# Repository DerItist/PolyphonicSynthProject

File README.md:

# PolyphonicSynthProject
All about building my own polyphonic synthesizer.

I use the open source tool KICAD for the schematics and pcb design.

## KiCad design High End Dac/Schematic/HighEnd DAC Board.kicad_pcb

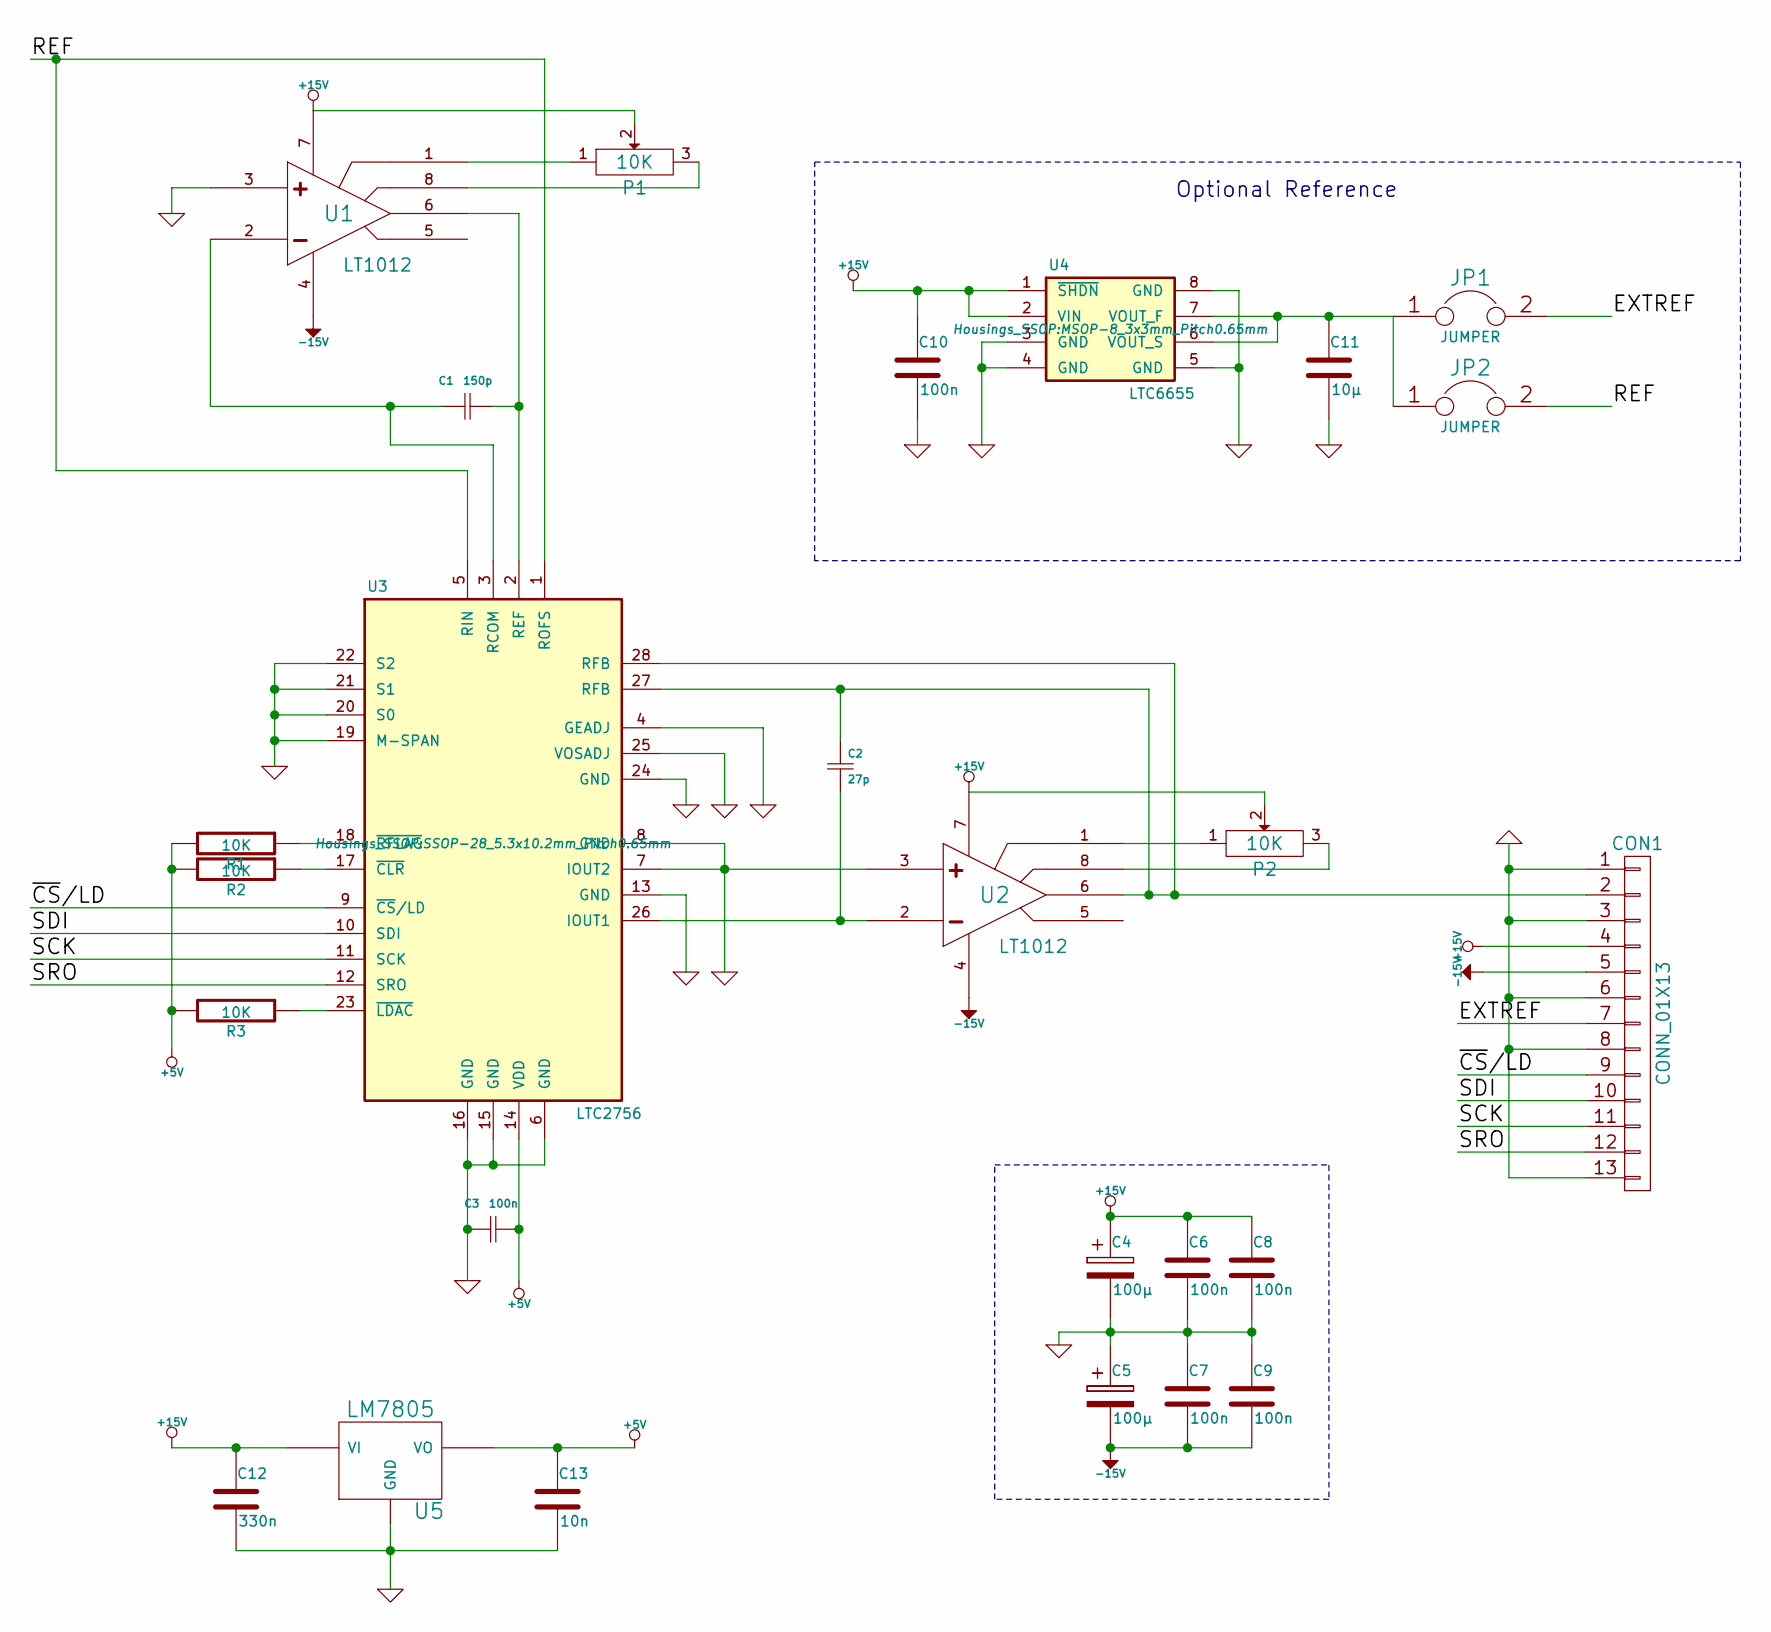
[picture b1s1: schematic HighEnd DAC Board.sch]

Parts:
C1: 150p; C_Disc_D3_P2.5
C2: 27p; C_Disc_D3_P2.5
C3: 100n; C_0805_HandSoldering
C4, C5: 100µ; Elko_vert_20x10mm_RM2.5to5_CopperClear
C6, C7, C8, C9, C10: 100n; C_Disc_D3_P2.5
C11: 10µ; C_Rect_L7.5_W6.5_P5
C12: 330n; C_Rect_L7.5_W6.5_P5
C13: 10n; C_Disc_D3_P2.5
CON1: CONN_01X13; DB15FD
JP1, JP2: JUMPER; Pin_Header_Straight_1x02
P1, P2: 10K; Potentiometer_Bourns_3296X_3-8Zoll_Inline_ScrewFront
R1, R2, R3: 10K; Resistor_Horizontal_RM10mm
U1, U2: LT1012; DIP-8__300_ELL
U3: LTC2756; SSOP-28_5.3x10.2mm_Pitch0.65mm
U4: LTC6655; MSOP-8_3x3mm_Pitch0.65mm
U5: LM7805; LM78XX-TO92

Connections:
+5V: C3.2, C13.1, R1.2, R2.2, R3.2, U3.14 (VDD), U5.VO
+15V: C4.1, C6.1, C8.1, C10.1, C12.1, CON1.4, P1.2, P2.2, U1.7 (V+), U2.7 (V+), U4.1 (~SHDN~), U4.2 (VIN), U5.VI
-15V: C5.2, C7.2, C9.2, CON1.5, U1.4 (V-), U2.4 (V-)
/EXTREF: CON1.7, JP1.2
/REF: JP2.2, U3.1 (ROFS), U3.5 (RIN)
/SCK: CON1.11, U3.11 (SCK)
/SDI: CON1.10, U3.10 (SDI)
/SRO: CON1.12, U3.12 (SRO)
/~CS~/LD: CON1.9, U3.9 (~CS~/LD)
GND: C3.1, C4.2, C5.1, C6.2, C7.1, C8.2, C9.1, C10.2, C11.2, C12.2, C13.2, CON1.1, CON1.3, CON1.6, CON1.8, CON1.13, U1.3 (NON), U2.3 (NON), U3.4 (GEADJ), U3.6 (GND), U3.7 (IOUT2), U3.8 (GND), U3.13 (GND), U3.15 (GND), U3.16 (GND), U3.19 (M-SPAN), U3.20 (S0), U3.21 (S1), U3.22 (S2), U3.24 (GND), U3.25 (VOSADJ), U4.3 (GND), U4.4 (GND), U4.5 (GND), U4.8 (GND), U5.GND
unnamed: C1.1, U1.2 (INVERTING), U3.3 (RCOM)
unnamed: C1.2, U1.6 (OUTPUT), U3.2 (REF)
unnamed: C2.1, CON1.2, U2.6 (OUTPUT), U3.27 (RFB), U3.28 (RFB)
unnamed: C2.2, U2.2 (INVERTING), U3.26 (IOUT1)
unnamed: C11.1, JP1.1, JP2.1, U4.6 (VOUT_S), U4.7 (VOUT_F)
unnamed: P1.1, U1.1 (VOS/TRIM)
unnamed: P1.3, U1.8 (VOS/TRIM)
unnamed: P2.1, U2.1 (VOS/TRIM)
unnamed: P2.3, U2.8 (VOS/TRIM)
unnamed: R1.1, U3.18 (~RFLAG)
unnamed: R2.1, U3.17 (~CLR)
unnamed: R3.1, U3.23 (~LDAC)

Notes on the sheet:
Optional Reference

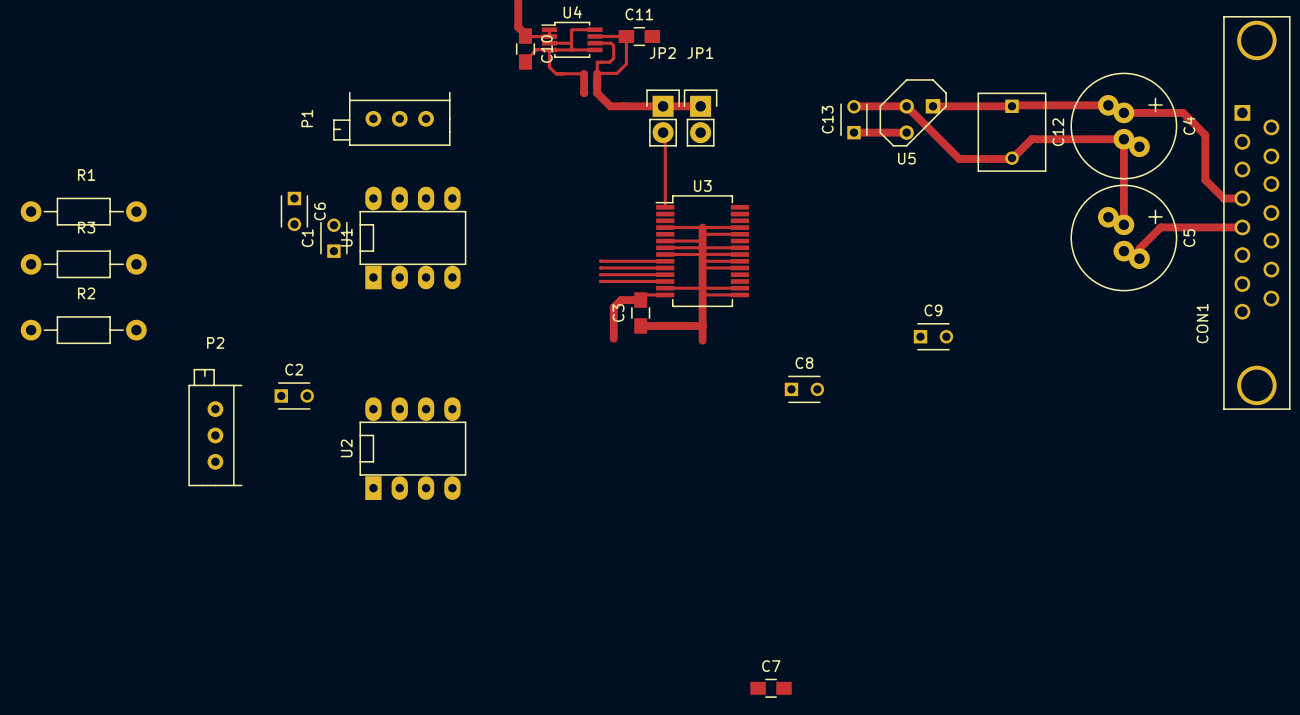
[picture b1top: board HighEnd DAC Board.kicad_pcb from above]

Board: 2 copper layers, 26 parts (0 on the bottom side), 22 nets.

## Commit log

2015-04-14 :circus_tent: Added .gitattributes & .gitignore files
2015-04-14 Pictures VCO
    Some Measurements of the VCO
2015-04-15 First draft of the High End DAC board.
    First draft of the High End DAC board.
    This board uses a 18 Bit DAC
2015-04-18 Create README.md
    initial Infos
2015-04-18 Added some PI Filter to the supply rails
    Added some PI Filter to the supply rails
2015-04-20 Added CS Style VCO LTspice
    Initial CS style VCO LTspice files
